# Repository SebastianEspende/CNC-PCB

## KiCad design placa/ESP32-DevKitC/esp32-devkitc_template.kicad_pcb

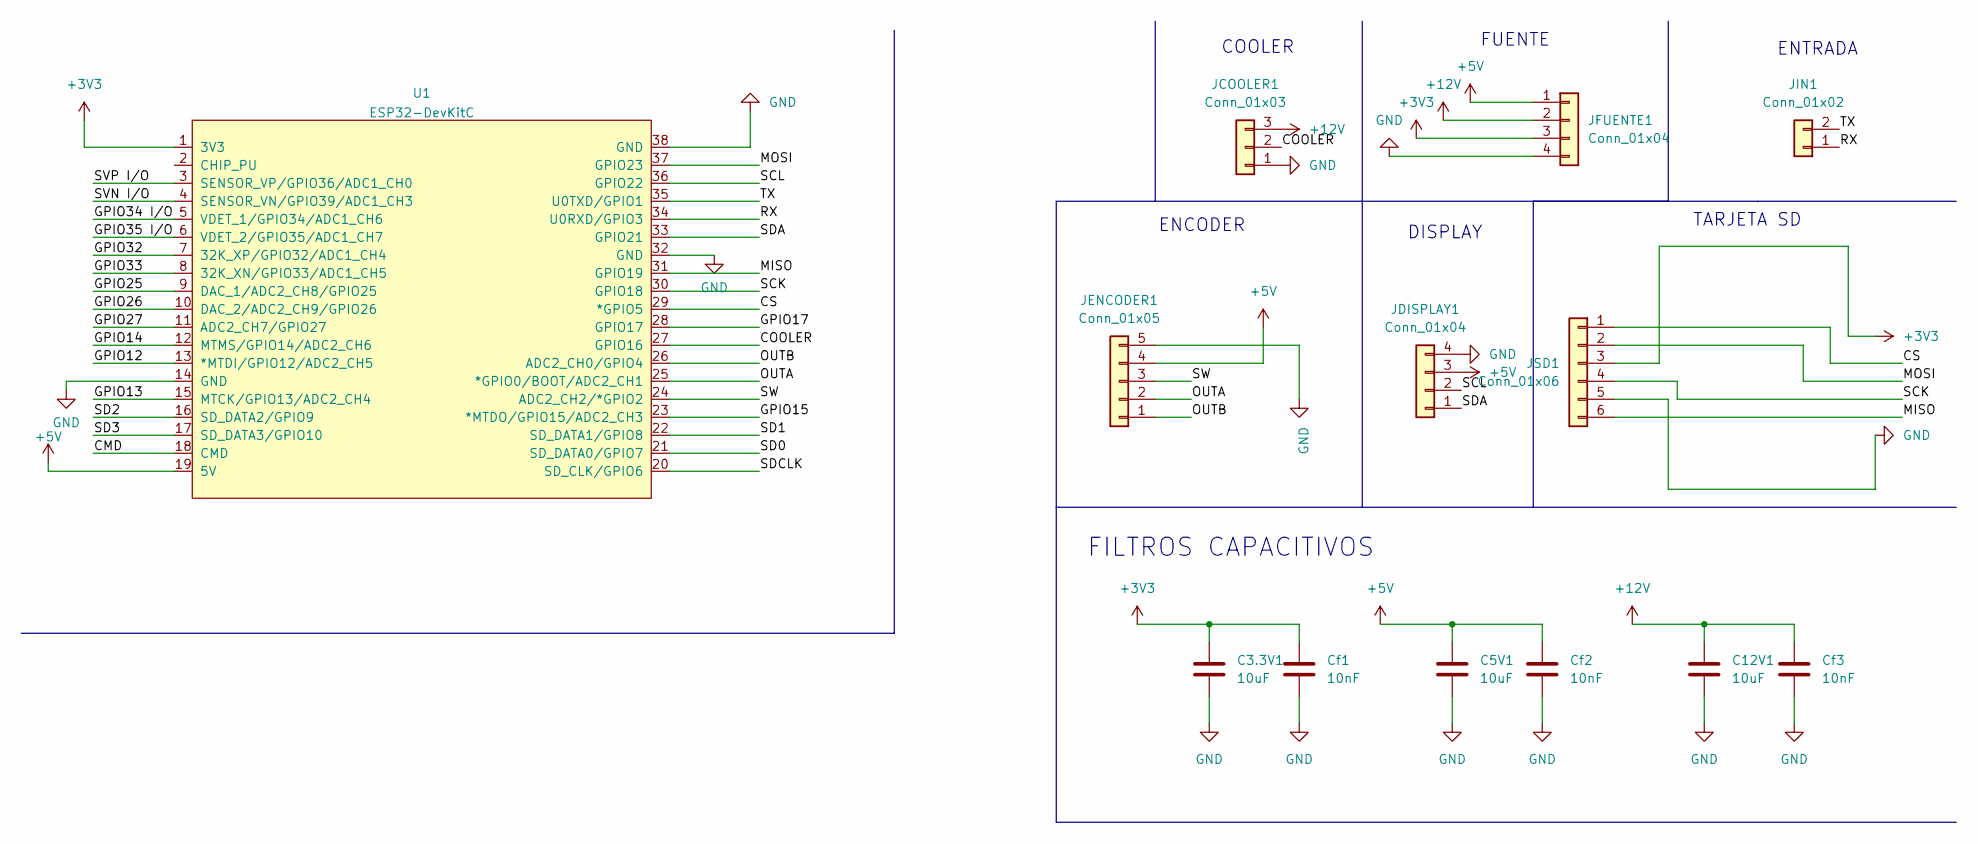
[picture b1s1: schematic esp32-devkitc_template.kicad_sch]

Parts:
C3.3V1, C5V1, C12V1: 10uF; CP_Radial_Tantal_D5.5mm_P2.50mm
Cf1, Cf2, Cf3: 10nF; C_Rect_L4.6mm_W2.0mm_P2.50mm_MKS02_FKP02
JCOOLER1: Conn_01x03; PinHeader_1x03_P2.54mm_Vertical
JDISPLAY1: Conn_01x04; PinSocket_1x04_P2.54mm_Vertical
JENCODER1: Conn_01x05; PinSocket_1x05_P2.54mm_Vertical
JFUENTE1: Conn_01x04; PinHeader_1x04_P2.54mm_Vertical
JIN1: Conn_01x02; PinHeader_1x02_P2.54mm_Vertical
JSD1: Conn_01x06; PinHeader_1x06_P2.54mm_Vertical
U1: ESP32-DevKitC

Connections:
+3V3: C3.3V1.1, Cf1.1, JFUENTE1.3, JSD1.3, U1.1 (3V3)
+5V: C5V1.1, Cf2.1, JDISPLAY1.3, JENCODER1.4, JFUENTE1.1, U1.19 (5V)
+12V: C12V1.1, Cf3.1, JCOOLER1.3, JFUENTE1.2
/CMD: U1.18 (CMD)
/COOLER: JCOOLER1.2, U1.27 (GPIO16)
/CS: JSD1.1, U1.29 (*GPIO5)
/GPIO12: U1.13 (*MTDI/GPIO12/ADC2_CH5)
/GPIO13: U1.15 (MTCK/GPIO13/ADC2_CH4)
/GPIO14: U1.12 (MTMS/GPIO14/ADC2_CH6)
/GPIO15: U1.23 (*MTDO/GPIO15/ADC2_CH3)
/GPIO17: U1.28 (GPIO17)
/GPIO25: U1.9 (DAC_1/ADC2_CH8/GPIO25)
/GPIO26: U1.10 (DAC_2/ADC2_CH9/GPIO26)
/GPIO27: U1.11 (ADC2_CH7/GPIO27)
/GPIO32: U1.7 (32K_XP/GPIO32/ADC1_CH4)
/GPIO33: U1.8 (32K_XN/GPIO33/ADC1_CH5)
/GPIO34 I/O: U1.5 (VDET_1/GPIO34/ADC1_CH6)
/GPIO35 I/O: U1.6 (VDET_2/GPIO35/ADC1_CH7)
/MISO: JSD1.6, U1.31 (GPIO19)
/MOSI: JSD1.2, U1.37 (GPIO23)
/OUTA: JENCODER1.2, U1.25 (*GPIO0/BOOT/ADC2_CH1)
/OUTB: JENCODER1.1, U1.26 (ADC2_CH0/GPIO4)
/RX: JIN1.1, U1.34 (U0RXD/GPIO3)
/SCK: JSD1.4, U1.30 (GPIO18)
/SCL: JDISPLAY1.2, U1.36 (GPIO22)
/SD0: U1.21 (SD_DATA0/GPIO7)
/SD1: U1.22 (SD_DATA1/GPIO8)
/SD2: U1.16 (SD_DATA2/GPIO9)
/SD3: U1.17 (SD_DATA3/GPIO10)
/SDA: JDISPLAY1.1, U1.33 (GPIO21)
/SDCLK: U1.20 (SD_CLK/GPIO6)
/SVN I/O: U1.4 (SENSOR_VN/GPIO39/ADC1_CH3)
/SVP I/O: U1.3 (SENSOR_VP/GPIO36/ADC1_CH0)
/SW: JENCODER1.3, U1.24 (ADC2_CH2/*GPIO2)
/TX: JIN1.2, U1.35 (U0TXD/GPIO1)
GND: C3.3V1.2, C5V1.2, C12V1.2, Cf1.2, Cf2.2, Cf3.2, JCOOLER1.1, JDISPLAY1.4, JENCODER1.5, JFUENTE1.4, JSD1.5, U1.14 (GND), U1.32 (GND), U1.38 (GND)

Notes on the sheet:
TARJETA SD
FUENTE
COOLER
FILTROS CAPACITIVOS
ENTRADA
ENCODER
DISPLAY

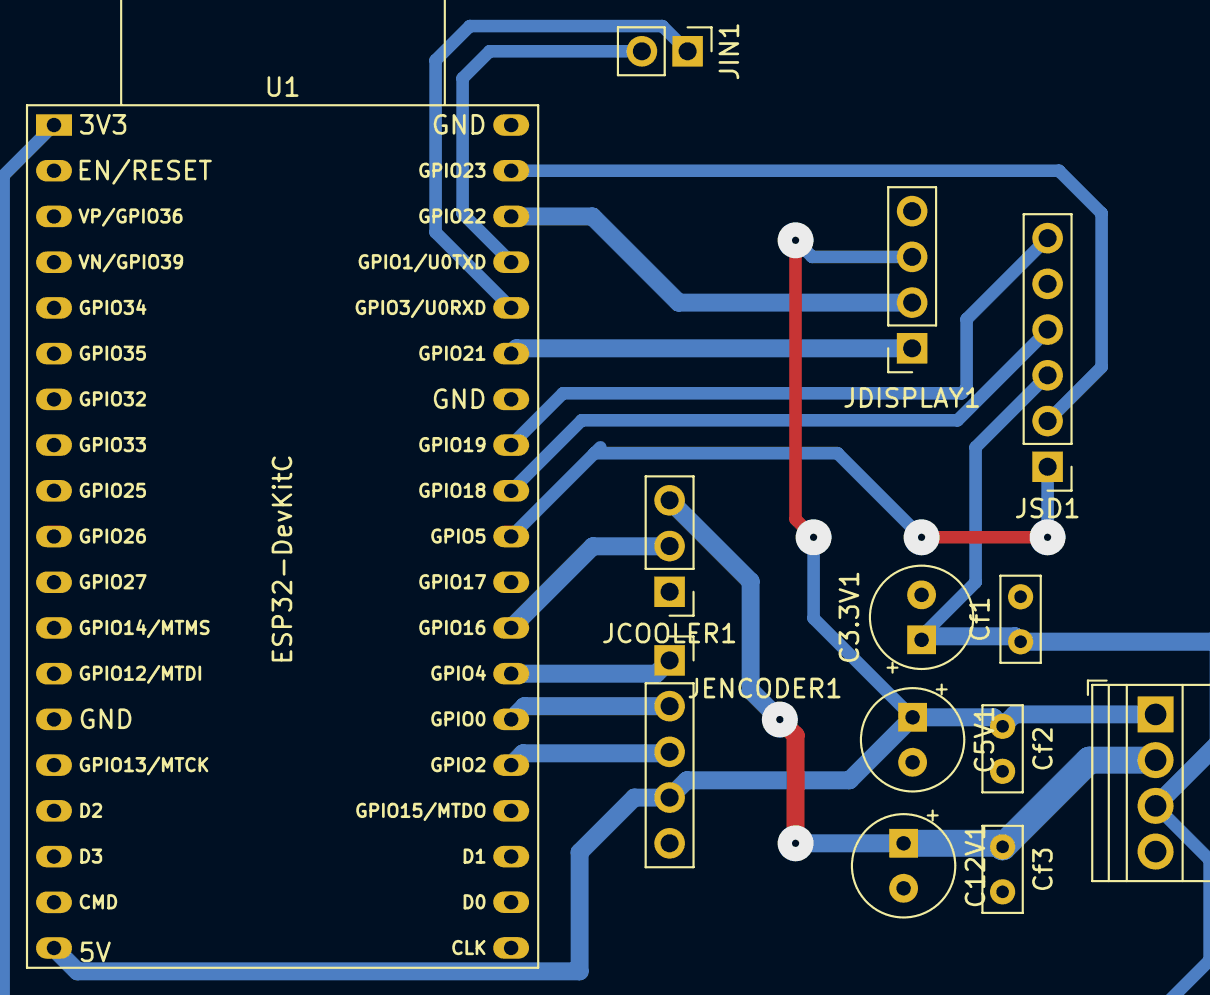
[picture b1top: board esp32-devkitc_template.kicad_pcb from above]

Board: 2 copper layers, 13 parts (0 on the bottom side), 16 nets.

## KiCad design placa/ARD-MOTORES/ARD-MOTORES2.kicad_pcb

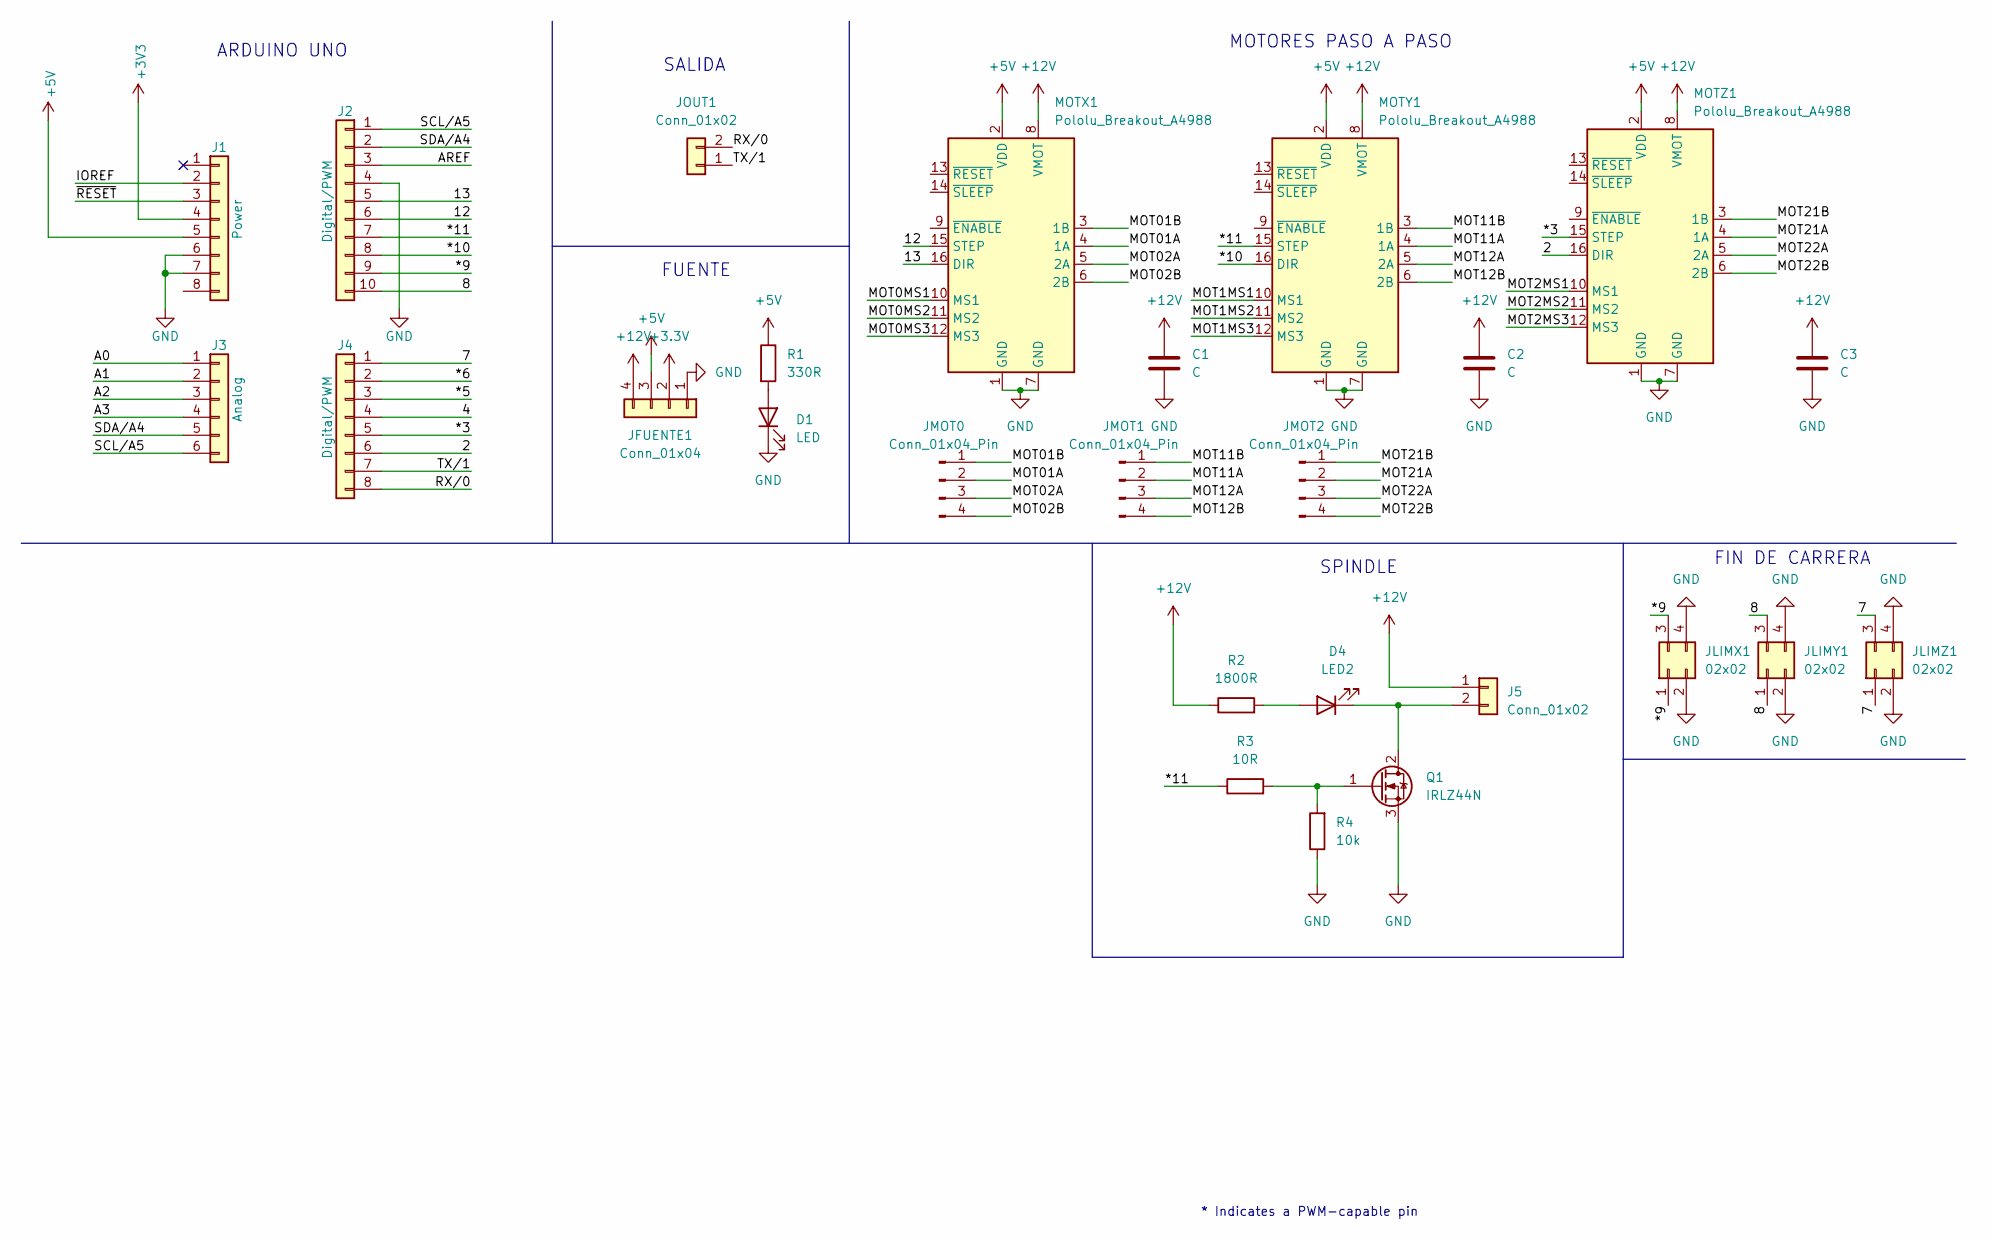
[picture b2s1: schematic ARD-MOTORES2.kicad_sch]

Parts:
C1, C2, C3: C; CP_Radial_D8.0mm_P3.80mm
D1: LED; LED_D3.0mm
D4: LED2; LED_D3.0mm
J1: Power; PinSocket_1x08_P2.54mm_Vertical
J2: Digital/PWM; PinSocket_1x10_P2.54mm_Vertical
J3: Analog; PinSocket_1x06_P2.54mm_Vertical
J4: Digital/PWM; PinSocket_1x08_P2.54mm_Vertical
J5: Conn_01x02; TerminalBlock_Phoenix_MKDS-1,5-2-5.08_1x02_P5.08mm_Horizont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
JFUENTE1: Conn_01x04; TerminalBlock_Xinya_XY308-2.54-4P_1x04_P2.54mm_Horizontal
JLIMX1: 02x02; PinSocket_2x02_P2.54mm_Vertical
JLIMY1: 02x02; PinSocket_2x02_P2.54mm_Vertical
JLIMZ1: 02x02; PinSocket_2x02_P2.54mm_Vertical
JMOT0, JMOT1, JMOT2: Conn_01x04_Pin; PinSocket_1x04_P2.54mm_Vertical
JOUT1: Conn_01x02; PinSocket_1x02_P2.54mm_Vertical
MOTX1: Pololu_Breakout_A4988; Pololu_Breakout-16_15.2x20.3mm
MOTY1: Pololu_Breakout_A4988; Pololu_Breakout-16_15.2x20.3mm
MOTZ1: Pololu_Breakout_A4988; Pololu_Breakout-16_15.2x20.3mm
Q1: IRLZ44N; TO-220-3_Vertical
R1: 330R; R_Axial_DIN0309_L9.0mm_D3.2mm_P12.70mm_Horizontal
R2: 1800R; R_Axial_DIN0309_L9.0mm_D3.2mm_P12.70mm_Horizontal
R3: 10R; R_Axial_DIN0309_L9.0mm_D3.2mm_P12.70mm_Horizontal
R4: 10k; R_Axial_DIN0309_L9.0mm_D3.2mm_P12.70mm_Horizontal

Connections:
+3.3V: JFUENTE1.2
+3V3: J1.4
+5V: J1.5, JFUENTE1.3, MOTX1.2 (VDD), MOTY1.2 (VDD), MOTZ1.2 (VDD), R1.1
+12V: C1.1, C2.1, C3.1, J5.1, JFUENTE1.4, MOTX1.8 (VMOT), MOTY1.8 (VMOT), MOTZ1.8 (VMOT), R2.1
/2: J4.6, MOTZ1.16 (DIR)
/4: J4.4
/7: J4.1, JLIMZ1.1, JLIMZ1.3
/8: J2.10, JLIMY1.1, JLIMY1.3
/12: J2.6, MOTX1.15 (STEP)
/13: J2.5, MOTX1.16 (DIR)
/*3: J4.5, MOTZ1.15 (STEP)
/*5: J4.3
/*6: J4.2
/*9: J2.9, JLIMX1.1, JLIMX1.3
/*10: J2.8, MOTY1.16 (DIR)
/*11: J2.7, MOTY1.15 (STEP), R3.1
/A0: J3.1
/A1: J3.2
/A2: J3.3
/A3: J3.4
/AREF: J2.3
/IOREF: J1.2
/MOT0MS1: MOTX1.10 (MS1)
/MOT0MS2: MOTX1.11 (MS2)
/MOT0MS3: MOTX1.12 (MS3)
/MOT01A: JMOT0.2, MOTX1.4 (1A)
/MOT01B: JMOT0.1, MOTX1.3 (1B)
/MOT1MS1: MOTY1.10 (MS1)
/MOT1MS2: MOTY1.11 (MS2)
/MOT1MS3: MOTY1.12 (MS3)
/MOT02A: JMOT0.3, MOTX1.5 (2A)
/MOT02B: JMOT0.4, MOTX1.6 (2B)
/MOT2MS1: MOTZ1.10 (MS1)
/MOT2MS2: MOTZ1.11 (MS2)
/MOT2MS3: MOTZ1.12 (MS3)
/MOT11A: JMOT1.2, MOTY1.4 (1A)
/MOT11B: JMOT1.1, MOTY1.3 (1B)
/MOT12A: JMOT1.3, MOTY1.5 (2A)
/MOT12B: JMOT1.4, MOTY1.6 (2B)
/MOT21A: JMOT2.2, MOTZ1.4 (1A)
/MOT21B: JMOT2.1, MOTZ1.3 (1B)
/MOT22A: JMOT2.3, MOTZ1.5 (2A)
/MOT22B: JMOT2.4, MOTZ1.6 (2B)
/RX/0: J4.8, JOUT1.2
/SCL/A5: J2.1, J3.6
/SDA/A4: J2.2, J3.5
/TX/1: J4.7, JOUT1.1
/~RESET: J1.3
GND: C1.2, C2.2, C3.2, D1.1 (K), J1.6, J1.7, J2.4, JFUENTE1.1, JLIMX1.2, JLIMX1.4, JLIMY1.2, JLIMY1.4, JLIMZ1.2, JLIMZ1.4, MOTX1.1 (GND), MOTX1.7 (GND), MOTY1.1 (GND), MOTY1.7 (GND), MOTZ1.1 (GND), MOTZ1.7 (GND), Q1.3 (S), R4.1
unnamed: D1.2 (A), R1.2
unnamed: D4.2 (A), R2.2
unnamed: D4.1 (K), J5.2, Q1.2 (D)
unnamed: Q1.1 (G), R3.2, R4.2

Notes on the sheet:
ARDUINO UNO
FUENTE
MOTORES PASO A PASO
* Indicates a PWM-capable pin
SALIDA
SPINDLE
FIN DE CARRERA

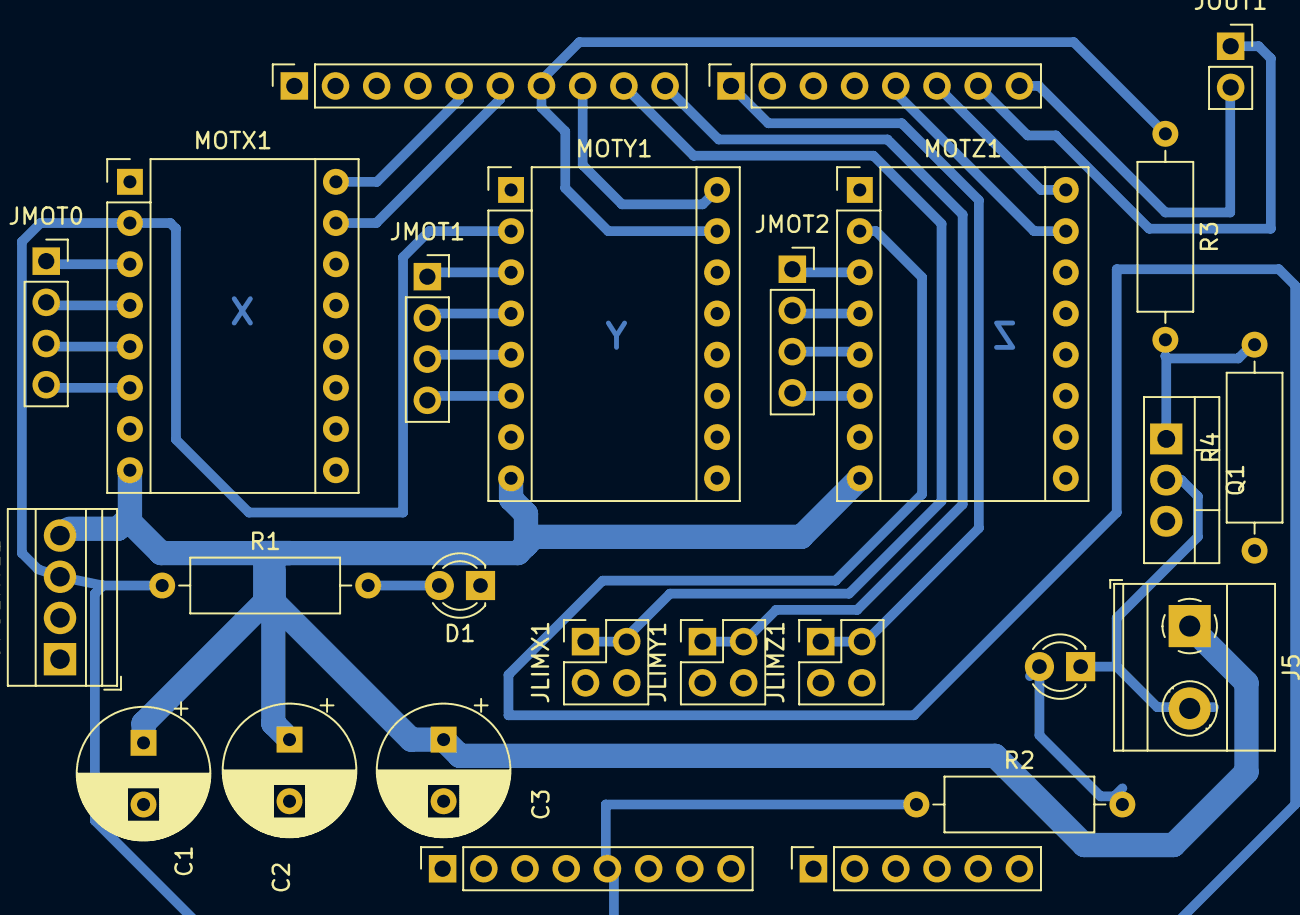
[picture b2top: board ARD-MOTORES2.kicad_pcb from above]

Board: 2 copper layers, 26 parts (0 on the bottom side), 32 nets.

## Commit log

2024-07-29 second commit
2024-08-01 placas
2024-08-01 arduino como main
2024-10-14 muchas cosas
2024-10-14 otras muchas cosas
2024-10-15 pruebasserver
2024-10-18 sever upload
2024-11-26 arduino codigo
2024-11-26 codigo esp32
2024-11-26 renombrado
